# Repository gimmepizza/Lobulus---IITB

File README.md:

# Lobulus---IITB
This is a non invasive glucose measurement device based on ultrasonic sensing

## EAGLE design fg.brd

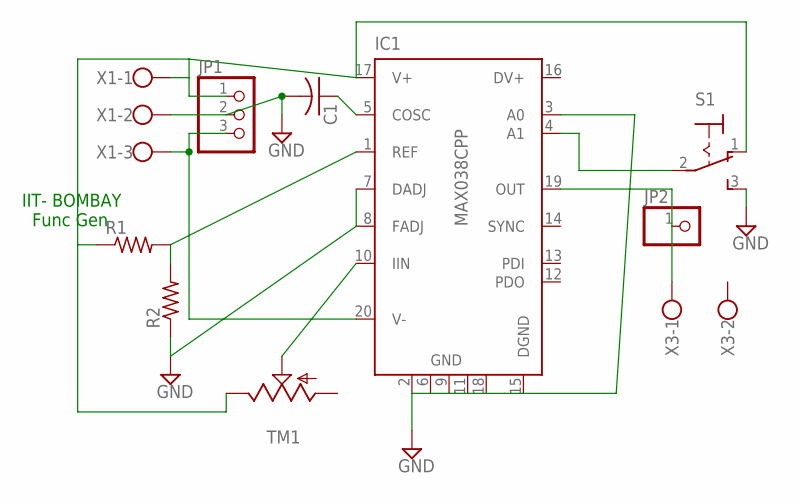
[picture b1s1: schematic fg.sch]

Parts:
C1: C-US050-045X075; C050-045X075
IC1: MAX038CPP; DIL20
JP1: PINHD-1X3CB; 1X03-CLEANBIG
JP2: PINHD-1X1CB; 1X01-CLEANBIG
R1, R2: R-US_0309/10; 0309/10
S1: 320-916
TM1: TRIM; 6MM
X1: W237-103
X3: W237-102

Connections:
DV+: IC1.16 (DV+)
GND: C1.2, IC1.2 (GND), IC1.3 (A0), IC1.6 (GND), IC1.7 (DADJ), IC1.8 (FADJ), IC1.9 (GND), IC1.11 (GND), IC1.15 (DGND), IC1.18 (GND), JP1.2, R2.1, S1.3 (S), X1.2
unnamed: IC1.17 (V+), JP1.1, R1.1, S1.1 (O), TM1.E, X1.1
unnamed: IC1.20 (V-), JP1.3, X1.3
unnamed: C1.1, IC1.5 (COSC)
unnamed: IC1.1 (REF), R1.2, R2.2
unnamed: IC1.10 (IIN), TM1.S
unnamed: IC1.19 (OUT), JP2.1, X3.1
unnamed: IC1.4 (A1), S1.2

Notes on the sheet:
IIT- BOMBAY Func Gen

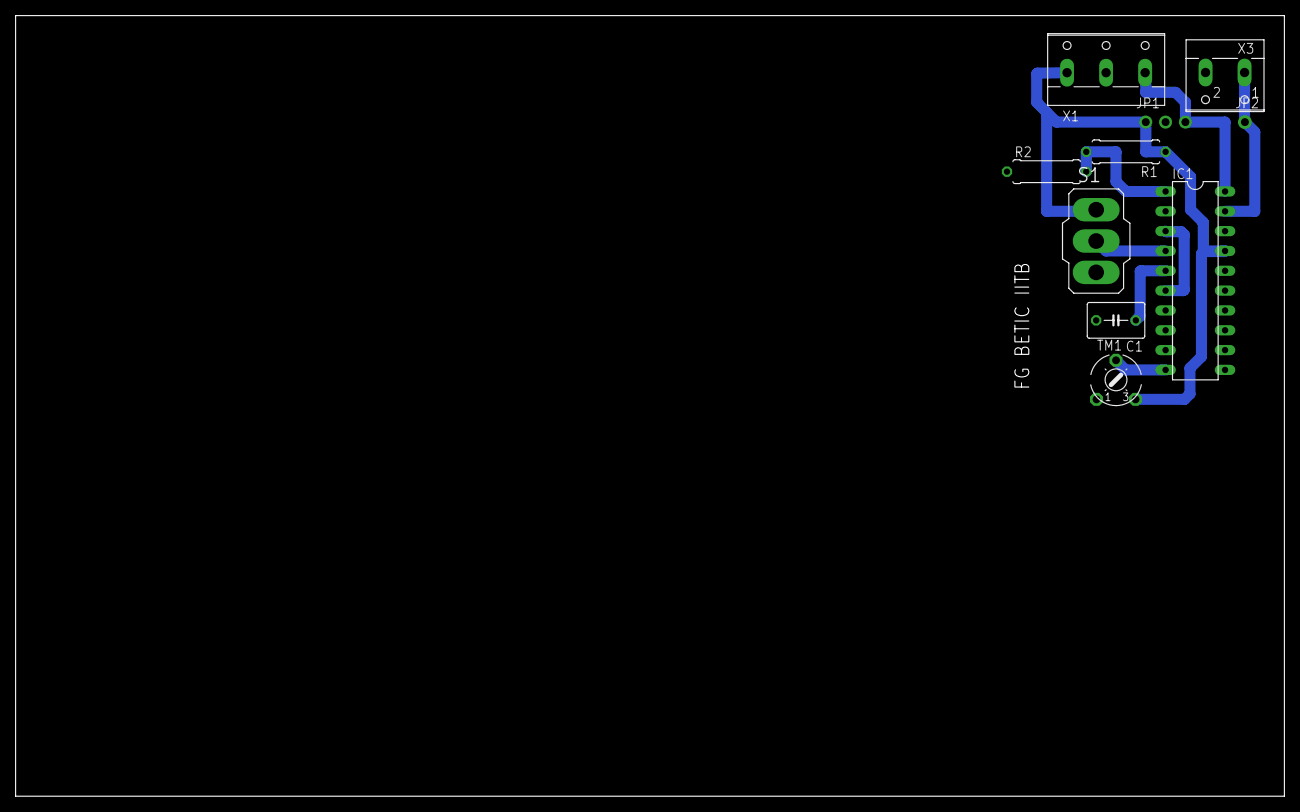
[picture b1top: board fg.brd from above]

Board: 2 copper layers, 162.5 x 100.0 mm, 10 parts (0 on the bottom side), 8 nets.

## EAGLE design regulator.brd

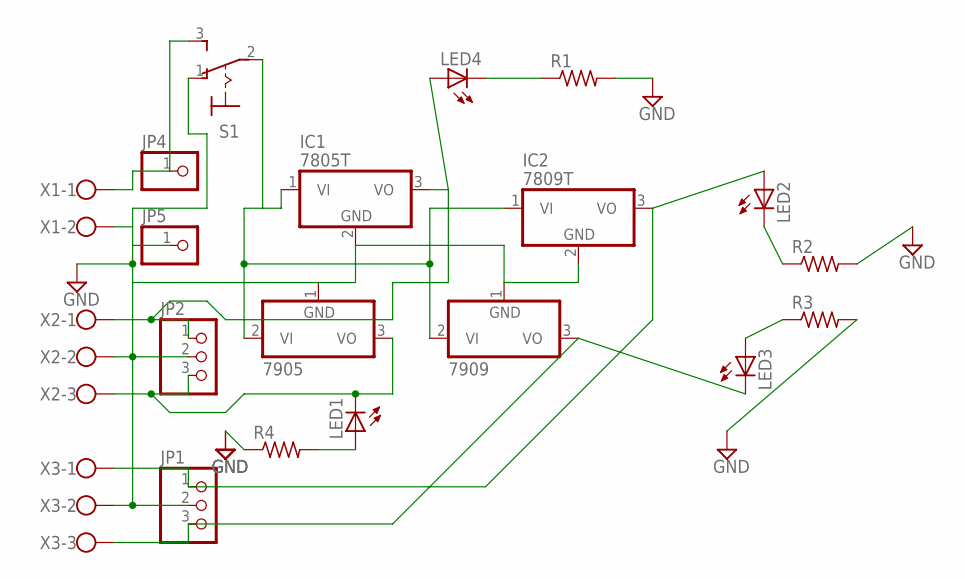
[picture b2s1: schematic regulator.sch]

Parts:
7905, 7909: 7905T; TO220H
IC1: 7805T; TO220H
IC2: 7809T; TO220H
JP1, JP2: PINHD-1X3CB; 1X03-CLEANBIG
JP4, JP5: PINHD-1X1CB; 1X01-CLEANBIG
LED1, LED2, LED3, LED4: LED3MM
R1, R2, R3, R4: R-US_0309/10; 0309/10
S1: 320-916
X1: W237-102
X2, X3: W237-103

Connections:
GND: 7905.1 (GND), 7909.1 (GND), IC1.2 (GND), IC2.2 (GND), JP1.2, JP2.2, JP5.1, R1.2, R2.2, R3.2, R4.1, S1.1 (O), X1.2, X2.2, X3.2
unnamed: 7905.2 (VI), 7909.2 (VI), IC1.1 (VI), IC2.1 (VI), S1.2
unnamed: JP4.1, S1.3 (S), X1.1
unnamed: LED4.K (C), R1.1
unnamed: LED2.K (C), R2.1
unnamed: LED1.A, R4.2
unnamed: 7905.3 (VO), JP2.3, LED1.K (C), X2.3
unnamed: IC2.3 (VO), JP1.1, LED2.A, X3.1
unnamed: LED3.A, R3.1
unnamed: 7909.3 (VO), JP1.3, LED3.K (C), X3.3
unnamed: IC1.3 (VO), JP2.1, LED4.A, X2.1

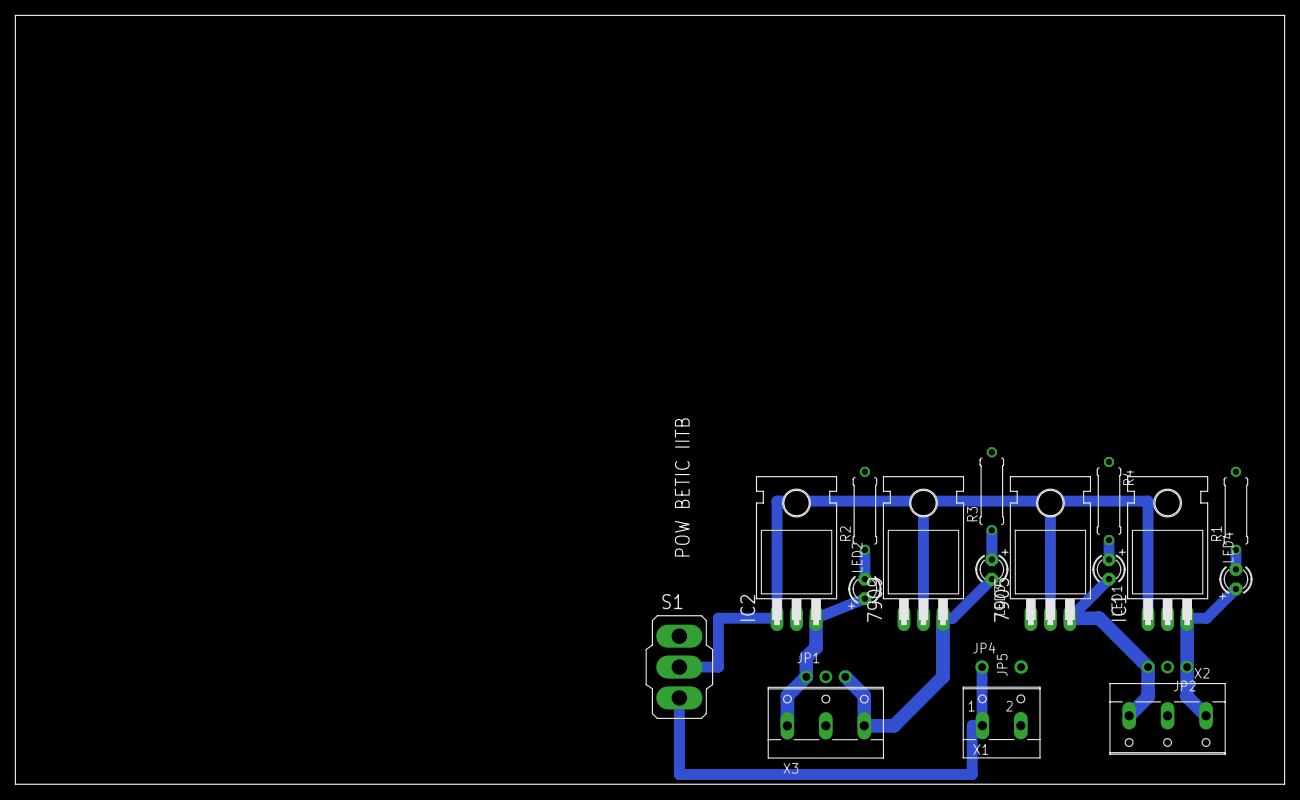
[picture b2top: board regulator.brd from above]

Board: 2 copper layers, 165.1 x 100.0 mm, 20 parts (0 on the bottom side), 11 nets.

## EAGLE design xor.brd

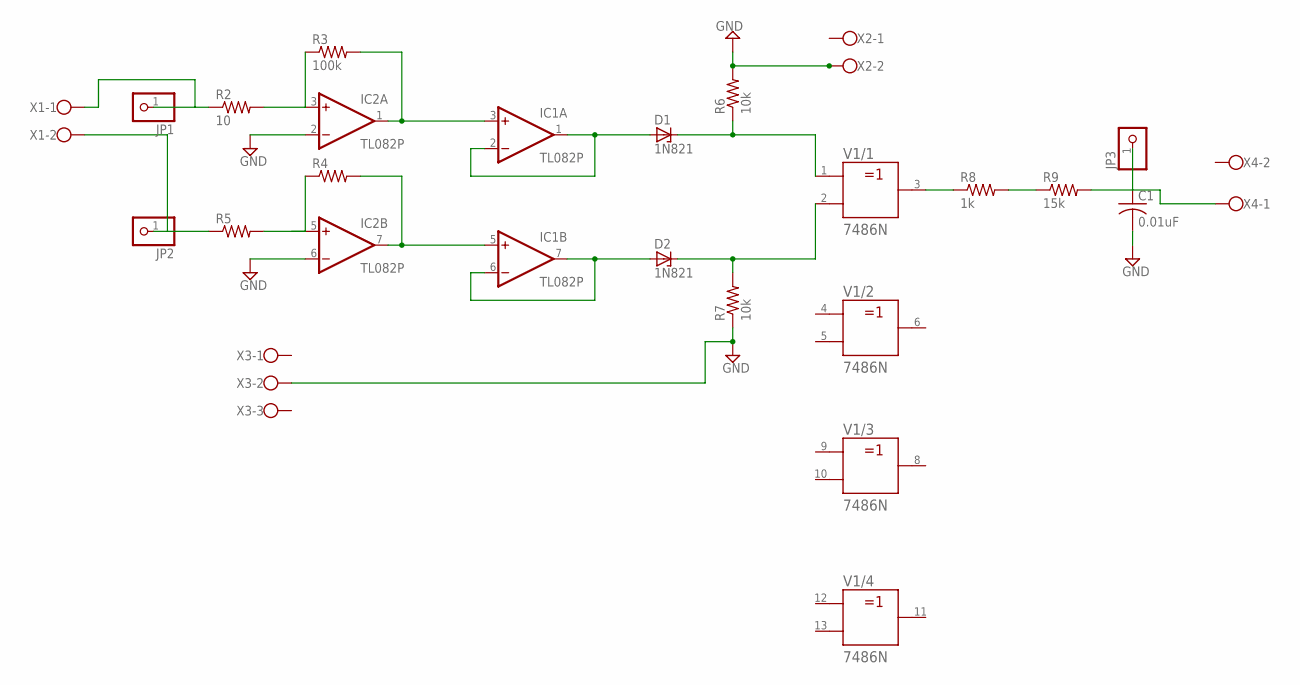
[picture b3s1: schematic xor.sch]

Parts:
C1: 0.01uF; C050-045X075
D1, D2: 1N821; DO35Z10
IC1, IC2: TL082P; DIL08
JP1, JP2, JP3: PINHD-1X1CB; 1X01-CLEANBIG
R2: 10; 0309/10
R3: 100k; 0309/10
R4, R5: R-US_0309/10; 0309/10
R6, R7: 10k; 0309/10
R8: 1k; 0309/10
R9: 15k; 0309/10
V1: 7486N; DIL14
X1, X2, X4: W237-102
X3: W237-103

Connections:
+UB: V1.14 (+UB)
-UB: V1.7 (-UB)
GND: C1.2, IC2.2 (-IN), IC2.6 (-IN), R6.2, R7.1, X2.2, X3.2
unnamed: IC2.3 (+IN), R2.2, R3.1
unnamed: IC1.3 (+IN), IC2.1 (OUT), R3.2
unnamed: IC2.5 (+IN), R4.1, R5.2
unnamed: IC1.5 (+IN), IC2.7 (OUT), R4.2
unnamed: D1.A, IC1.1 (OUT), IC1.2 (-IN)
unnamed: D2.A, IC1.6 (-IN), IC1.7 (OUT)
unnamed: D1.C, R6.1, V1.1 (A)
unnamed: D2.C, R7.2, V1.2 (B)
unnamed: R8.1, V1.3 (Y)
unnamed: R8.2, R9.1
unnamed: C1.1, JP3.1, R9.2, X4.1
unnamed: JP1.1, R2.1, X1.1
unnamed: JP2.1, R5.1, X1.2
V+: IC1.8 (V+), IC2.8 (V+)
V-: IC1.4 (V-), IC2.4 (V-)

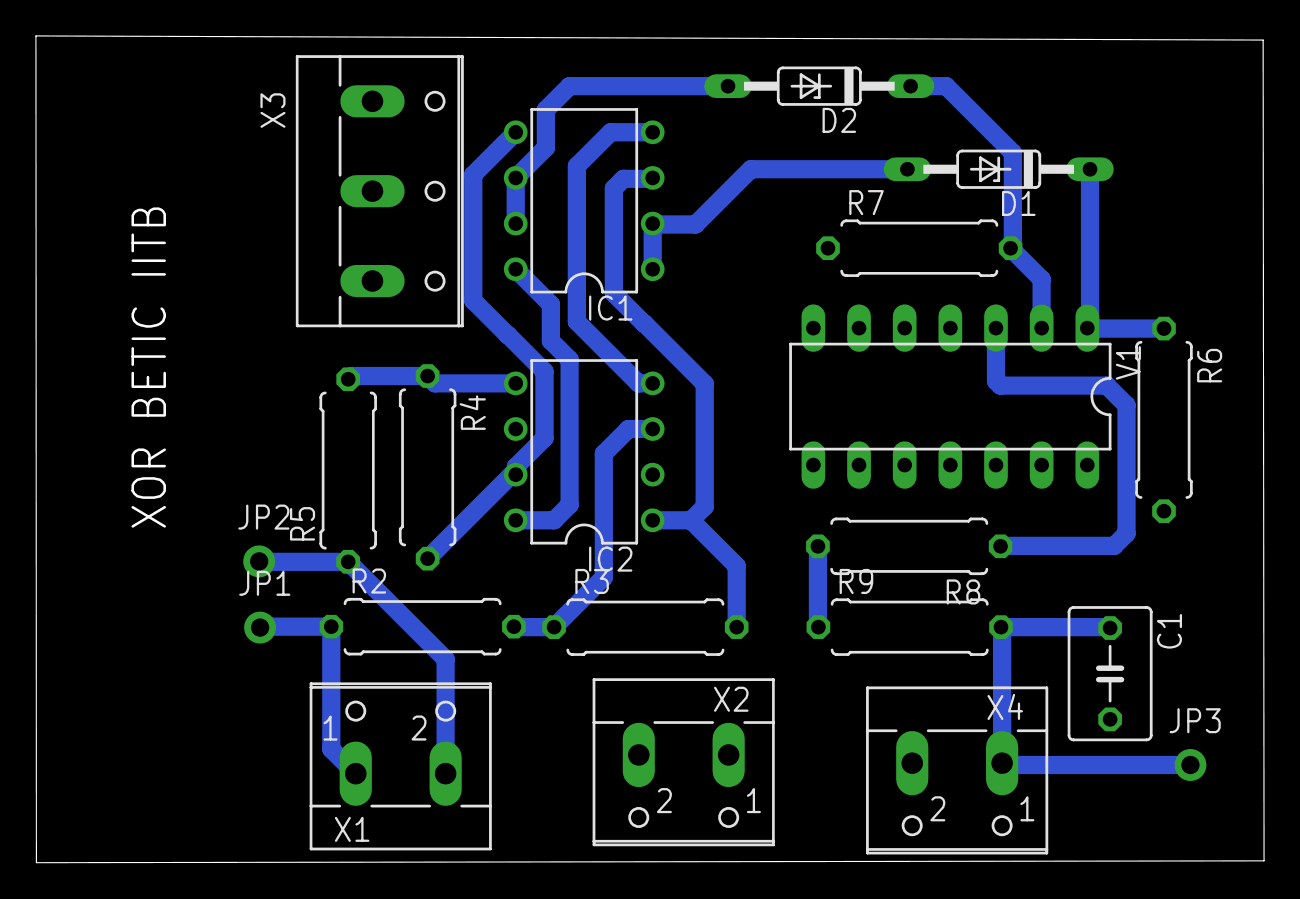
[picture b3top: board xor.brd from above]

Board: 2 copper layers, 68.3 x 46.0 mm, 21 parts (0 on the bottom side), 16 nets.

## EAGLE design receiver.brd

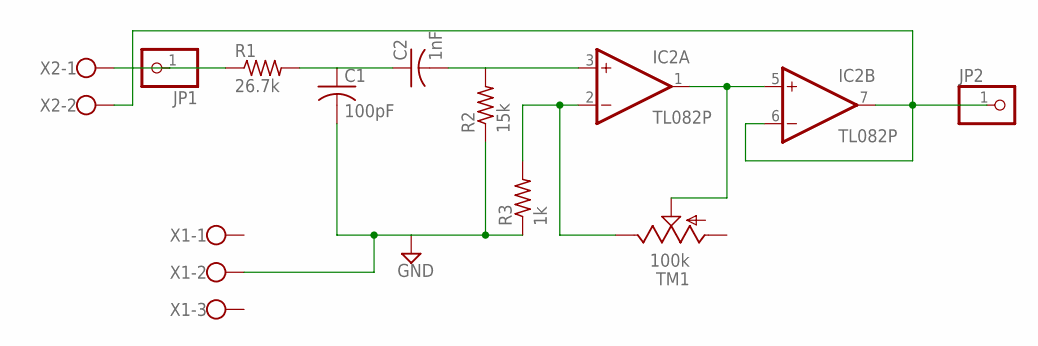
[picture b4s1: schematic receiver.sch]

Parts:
C1: 100pF; C050-045X075
C2: 1nF; C050-045X075
IC2: TL082P; DIL08
JP1, JP2: PINHD-1X1CB; 1X01-CLEANBIG
R1: 26.7k; 0309/10
R2: 15k; 0309/10
R3: 1k; 0309/10
TM1: 100k; 6MM
X1: W237-103
X2: W237-102

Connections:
GND: C1.2, R2.1, R3.1, X1.2
unnamed: JP1.1, R1.1, X2.1
unnamed: C1.1, C2.1, R1.2
unnamed: C2.2, IC2.3 (+IN), R2.2
unnamed: IC2.2 (-IN), R3.2, TM1.E
unnamed: IC2.1 (OUT), IC2.5 (+IN), TM1.S
unnamed: IC2.6 (-IN), IC2.7 (OUT), JP2.1, X2.2
V+: IC2.8 (V+)
V-: IC2.4 (V-)

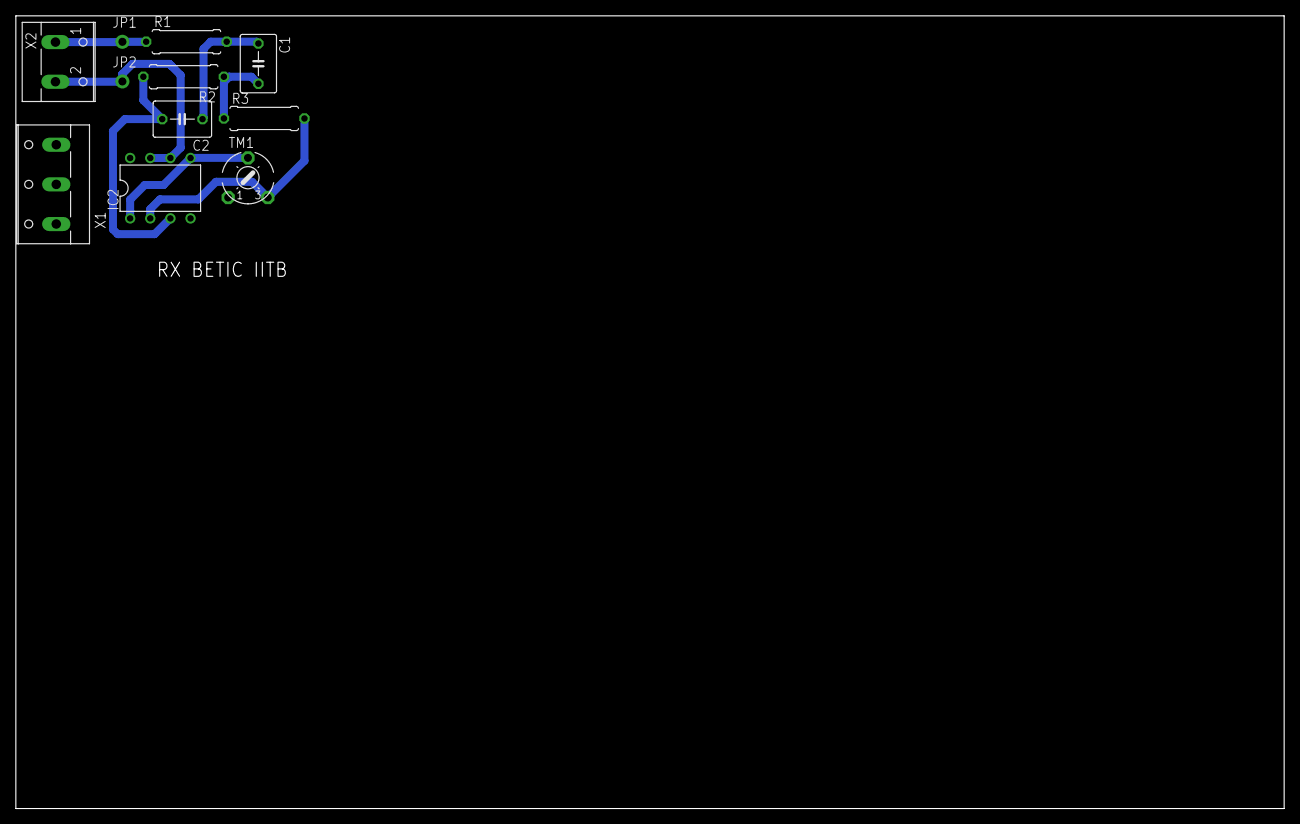
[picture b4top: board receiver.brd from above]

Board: 2 copper layers, 160.0 x 100.0 mm, 11 parts (0 on the bottom side), 7 nets.
